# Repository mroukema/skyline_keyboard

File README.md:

# Skyline Keyboard   
`v0.9`

Source files for the vista keyboard project

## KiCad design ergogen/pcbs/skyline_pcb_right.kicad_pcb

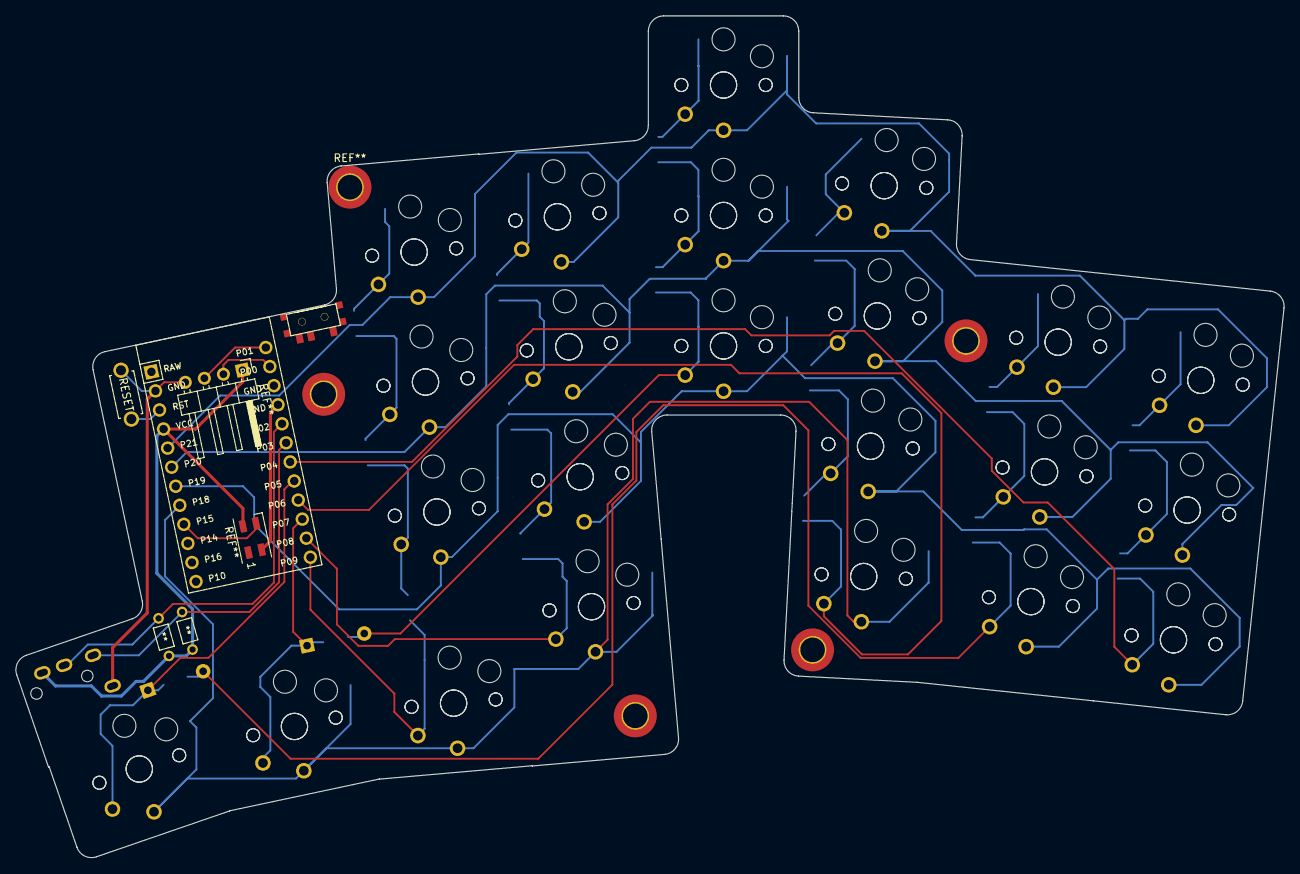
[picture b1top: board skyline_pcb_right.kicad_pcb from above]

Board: 2 copper layers, 165.2 x 109.7 mm, 68 parts (0 on the bottom side), 16 nets.

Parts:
**: R
**#2: R
D1, D2, D3, D4, D5, D6, D7, D8, D9, D10, D11, D12, D13, D14, D15, D16, D17: ComboDiode
MCU1: ProMicro
RSW1: SW_PUSH; ResetSW_1side
S1, S2, S3, S4, S5, S6, S7, S8, S9, S10, S11, S12, S13, S14, S15, S16, S17, S18, S19, S20, S21, S22, S23, S24, S25, S26, S27, S28, S29, S30, S31, S32, S33, S34, S35, S36, S37, S38, S39, S40, S41, S42, S43, S44, S45, S46: PG1350
T1: SPDT_C128955

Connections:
GND: MCU1.2, MCU1.15, MCU1.16, RSW1.1
P2: **#2.2, MCU1.17
P3: **.3, MCU1.18
P4: D1.1, D1.2, D2.1, D2.2, MCU1.19, S1.1, S2.1, S3.1, S4.1, S5.1, S6.1
P5: D3.1, D3.2, D4.1, D4.2, D17.1, D17.2, MCU1.20, S7.1, S8.1, S9.1, S10.1, S11.1, S12.1, S45.1, S46.1
P6: D5.1, D5.2, D6.1, D6.2, D7.1, D7.2, MCU1.21, S13.1, S14.1, S15.1, S16.1, S17.1, S18.1, S19.1, S20.1
P7: D8.1, D8.2, D9.1, D9.2, D16.1, D16.2, MCU1.22, S21.1, S22.1, S23.1, S24.1, S25.1, S26.1, S43.1, S44.1
P8: D10.1, D10.2, D11.1, D11.2, D12.1, D12.2, MCU1.23, S27.1, S28.1, S29.1, S30.1, S31.1, S32.1, S33.1, S34.1
P9: D13.1, D13.2, D14.1, D14.2, D15.1, D15.2, MCU1.24, S35.1, S36.1, S37.1, S38.1, S39.1, S40.1, S41.1, S42.1
P18: MCU1.8, S13.2, S14.2, S27.2, S28.2, S41.2, S42.2, S43.2, S44.2, S45.2, S46.2
P19: MCU1.7, S1.2, S2.2, S7.2, S8.2, S15.2, S16.2, S21.2, S22.2, S29.2, S30.2, S35.2, S36.2
P20: MCU1.6, S3.2, S4.2, S9.2, S10.2, S17.2, S18.2, S23.2, S24.2, S31.2, S32.2, S37.2, S38.2
P21: MCU1.5, S5.2, S6.2, S11.2, S12.2, S19.2, S20.2, S25.2, S26.2, S33.2, S34.2, S39.2, S40.2
RST: MCU1.3, RSW1.2
VCC: **.4, **#2.4, MCU1.4
undefined: T1.1, T1.2

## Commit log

2022-06-14 Add Initial readme
2022-06-14 Add current iteration of ergogen file
2022-06-14 Add preview for the current iteration of keyboard to readme
2022-06-14 Cleanup readme
2022-06-14 Fix issues with net defs
2022-06-14 Improved use of variables
    Add to pcb config (wip)
2022-06-14 Add more pcb details
2022-06-15 Fix some component posistions
2022-06-15 Update some component pos and scale panel too match.
    Add some offsets too account for diffs in ergogen and kicad footprint
    differences
2022-06-15 Update component pos's
2022-06-15 Rename yaml to file to match repo name change
2022-06-15 Updated outline svg
2022-06-15 Update readme to reflect name change
2022-06-15 Bump version to reflect progress towards completion
2022-06-16 Add experiments in adding 3dConnection footprint
2022-06-17 Diode positioning and row/column net work
2022-06-17 Fix typo
2022-06-17 Update pcb name
2022-07-15 update with lastest
2022-08-08 push latest work to remote
2022-08-11 Modify for use with choc spacing
2022-10-04 Add all files used in v 1.0 build
2022-10-04 Add the QMK config for skyline keyboard here for safe keeping
2022-10-05 Inital working version of personal config
2022-10-05 Update keymap and add layout def
2022-10-06 Update with current keymap and design files
2022-10-06 add git ignore
2022-10-19 Update keymap with latest additions
2023-05-04 Latest keymap
